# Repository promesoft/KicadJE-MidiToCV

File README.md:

# Kicad-MidiToCV
Midi to CV in Eurorack or as standalone

## Status - Rev B - Ongoing PCB layout and Sch update
Set on hold - MK2 is in progress ATM
## Status - Rev A Mounted - Midi code in progress
| Stage  | Detail | Status |
| ------------- | ------------- | ------------- |
| create material  | sch/pcb | produced Rev A  |
| | gerber | produced and uploaded RevA |
| production  | ordered  | OK |
|  | produced | OK |
|  | delivered | OK |
| ------------- | ------------- | ------------- |
| SOFTWARE | LFO | OK |
| SOFTWARE | MIDI MAP | OK - Stage 1 |
| SOFTWARE | CV | Ongoing |

## Preliminary validation
| Test  | Detail | Status |
| ------------- | ------------- | ------------- |
| Initial Inspection | Visual - Component Mounting | NOT OK |
| Initial Technical Test | Base operation | MIDI OUT NOT OK |
| | Knobs | OK |
| Initial Technical Test | MIDI IN | OK |
| Initial Technical Test | MIDI OUT | OK (to USB adapter) |
| Initial Product Test | MIDI IN/OUT MAPPER| OK |
| Initial Product Test | MIDI IN / CV OUT / GATE OUT| OK |
| Initial Product Test | LFO OUT| OK (use different pinout) |

## Secondary validation
| Test  | Detail | Status |
| ------------- | ------------- |------------- |
| Product Test | MIDI IN/OUT| OUT - FAIL on Roland keyboard |
| Product Test | LFO on DIO6 and 9 with ext RC | OK ! |
| Quality | LFO | Very usable |
| Quality | MIDI IN | |
| Quality | MIDI to CV | |
| Quality | MIDI to GATE | |
| Long Term Product Test | MIDI IN |  |
| Long Term Product Test | CV OUT |  |
| Long Term Product Test | GATE OUT |  |
| Long Term Product Test | LFO OUT | OK |
### Issues and Notes
Please note that the PIN1 and PIN2 are GATE. This is note described clearly in http://www.doepfer.de/a100_man/a100t_e.htm and needs to be noted when soldering the IDC header or when cabling if a Pin header has been mounted.
 * The two pots on the breakout board are too close for adding a knob
 * The orientation of the pinheader for the MCP4725 module - if mounted incorrectly the magic smoke disappears
 * 0R could be replaced with SMD jumpers
 * Consider a 200 mA fuse for Vin and 50mA for +5V pwr
 * The mounting hole that is off center is not matching both boards
### Errata
 * Footprint of PJ-321 has too small drill holes (1mm) - major
 * Footprint of PJ-321 is too narrow in the rear end :) - minor issue
 * Midi out circuit is WRONG - Major
### Workarounds
* Midi out not working - PCB workaround mod partially possible for voltage controlled inputs.
 * --Remove GND around DIN pin 5 (bottom copper side)
 * --Cut GND track to DIN pin 5 (top copper side)
 * --Remove Q1, R6, R9
 * --Connect 220R THT to base pad on Q1
 * --Connect C and E on Q1
 * --Add GND wire to pin2 of MIDI out DIN
## Physical Construction
 - 100x100mm
 - Separate unit with no alteration
 - Optional split in 2 for eurorack mount mirrored config

## Vital Components
 - Arduino Nano - where the magic lives (remember to socket it to be able to reprogram it)
 - Jack connectors: PJ-321 (important for the footprint)
 - KY-40 Encoder module (important for the pullup, footprint and 3D alignment)
 - MCP4825 module - if chosen (important for CV out function - footprint needs to match)
 If these are chosen the last two CV jacks should be ommitted.
 - MCP4728 chip - if chosen (important for the last 2 CV out)

## MIDI Board Features
### Single board - MIDI I/O and MIDI to CV
The board can be used as is for a prototype development of MIDI to CV
### Split board Eurorack - MIDI I/O and MIDI to CV
The board can be devided in two and combined front to front with spacers for a MIDI to CV eurorack module.
### Base board Eurorack - MIDI I/O
If only MIDI features are required the base board can work without the IO section.

## Generic Board Features
### Split board Options
The main board (with the arduino) has a couple of headers that can be connected to a different interface board using I2C, Analogue Inputs and Digital I/O.
### Non MIDI board
The MIDI components can be omitted if the features does not require MIDI, like an LFO, VCO or ADSR circuit.

## Base Construction
Arduino Nano based Controller and MIDI decoder.

### MIDI In
MIDI In through a PC814 (or optional PC817) Optocoupler and into the RX pin on the Arduino

### Midi Out
Optional expansion

### Gate
Gate pins from Arduino

## CV Out
I2C Dac with 2 options
### I2C Dac - Option 1 - Two Single channel DAC
2x MCP4725 DAC 
### I2C Dac - Option 2 - One 4 channel DAC
1x MCP4728

# RevB

# RevA

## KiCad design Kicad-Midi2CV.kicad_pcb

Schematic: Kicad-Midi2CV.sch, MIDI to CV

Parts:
A1: Arduino_Nano_v3.x; Arduino_Nano
C1: 100uF; CP_Radial_D5.0mm_P2.50mm
C2, C3, C5, C7, C8: 100n; C_0805_2012Metric_Pad1.15x1.40mm_HandSolder
C4, C6: 100uF 16v; CP_Radial_D5.0mm_P2.50mm
C9, C10, C11: 10n; C_0805_2012Metric_Pad1.15x1.40mm_HandSolder
D1: LED1; LED_D3.0mm_Horizontal_O6.35mm_Z6.0mm
D2: LED2; LED_D3.0mm_Horizontal_O6.35mm_Z6.0mm
D3: LED3; LED_D3.0mm_Horizontal_O6.35mm_Z6.0mm
D4: LED4; LED_D3.0mm_Horizontal_O6.35mm_Z6.0mm
D5: LEDset1; LED_D3.0mm_Horizontal_O6.35mm_Z6.0mm
D6: LEDset2; LED_D3.0mm_Horizontal_O6.35mm_Z6.0mm
IC1, IC2: MCP4725module; PinSocket_1x06_P2.54mm_Vertical
J1: Doepfer connector; PinSocket_2x08_P2.54mm_Vertical
J2: Vin 7-12v; BarrelJack_CUI_PJ-063AH_Horizontal
J3: MIDI OUT; din-5
J4: CV6 in; AudioJack3StereoNarrow-PJ-321
J5: Power Conn; PinHeader_1x04_P2.54mm_Vertical
J6: CV1; AudioJack3StereoNarrow-PJ-321
J7: CV2; AudioJack3StereoNarrow-PJ-321
J8: MIDI IN; din-5
J9: CV3; AudioJack3StereoNarrow-PJ-321
J10: CV4; AudioJack3StereoNarrow-PJ-321
J11: Gate1; AudioJack3StereoNarrow-PJ-321
J12, J18: GateConn; PinSocket_1x06_P2.54mm_Vertical
J13: Gate2; AudioJack3StereoNarrow-PJ-321
J14: Gate3; AudioJack3StereoNarrow-PJ-321
J15: Gate4; AudioJack3StereoNarrow-PJ-321
J16, J17: I2C_Conn; PinSocket_1x06_P2.54mm_Vertical
J19: CV7 in; AudioJack3StereoNarrow-PJ-321
J20: CV3 in; AudioJack3StereoNarrow-PJ-321
Q1, Q2: MMBT2222A; SOT-23_Handsoldering
R1, R2, R4, R5, R8, R10, R24, R25, R26, R27, R28: 10k; R_0805_2012Metric_Pad1.15x1.40mm_HandSolder
R3: 10M; R_0805_2012Metric_Pad1.15x1.40mm_HandSolder
R6, R9, R13, R15, R29: 1k; R_0805_2012Metric_Pad1.15x1.40mm_HandSolder
R7, R14: 220R; R_0805_2012Metric_Pad1.15x1.40mm_HandSolder
R11, R12: 8k2; R_0805_2012Metric_Pad1.15x1.40mm_HandSolder
R16, R17: 0R; R_0805_2012Metric_Pad1.15x1.40mm_HandSolder
R18, R19, R20, R21, R22, R23: 680R; R_0805_2012Metric_Pad1.15x1.40mm_HandSolder
RV1, RV2: 10k; Potentiometer_Alps_RK097_Single_Horizontal
SW1: KY40_Rotary_Encoder_Module; KY-40-rotary-encoder-board
U1: TL072; AJ_SO-8_5.3x6.2mm_P1.27mm
U2: EL814; DIP-4_W7.62mm_LongPads
U3: MCP4728; MSOP-10_3x3mm_P0.5mm

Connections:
+5V: A1.27, C3.2, IC1.5, IC2.5, J1.5, J1.6, J5.2, J16.6, J17.6, R3.1, R6.2, R11.2, R12.2, R13.2, SW1.5V, U2.4, U3.1
/12v: C4.1, C5.2, J1.7, J1.8, U1.8 (V+)
/-12v: C6.2, C7.1, J1.15, J1.16, U1.4 (V-)
/CV: J1.3, J1.4, R29.2
/Gate: J1.1, J1.2
/LDAC: A1.16, J16.4, J17.4, U3.4
/MIDI-IN: Q2.1, R15.2, U2.3
/MIDI-OUT: Q1.3, R6.1, R7.1
/RDY-BSY: A1.15, J16.5, J17.5, U3.5
/RX: A1.2, Q2.3, R13.1
/SCL: A1.24, IC1.3, IC2.3, J16.2, J17.2, R12.1, U3.2
/SDA: A1.23, IC1.4, IC2.4, J16.3, J17.3, R11.1, U3.3
/TX: A1.1, Q1.1, R9.2
/Vout1: IC1.1, R16.2
/Vout2: IC2.1, R17.2
A1: A1.20, C10.1, SW1.CLK
A2: A1.21, C11.1, SW1.DT
A3: A1.22, R27.2, R28.1
A6: A1.25, J12.5, J18.5, R8.2, R10.1
A7: A1.26, J12.6, J18.6, R25.2, R26.1, R29.1
Btn: A1.19, C9.1, R24.1
CV1: R16.1, U1.3 (+), U3.6
CV1Gain: J6.T, RV1.2, RV1.3, U1.1
CV2: R17.1, U1.5 (+), U3.7
CV2Gain: J7.T, RV2.2, RV2.3, U1.7
CV3: J9.T, U3.8
CV4: J10.T, U3.9
GND: A1.4, A1.29, C1.2, C2.2, C3.1, C4.2, C5.1, C6.1, C7.2, C8.1, C9.2, C10.2, C11.2, D1.1, D2.1, D3.1, D4.1, D5.1, D6.1, IC1.2, IC1.6, IC2.2, IC2.6, J1.9, J1.10, J1.11, J1.12, J1.13, J1.14, J2.2, J3.5, J4.S, J5.4, J6.S, J7.S, J9.S, J10.S, J11.S, J13.S, J14.S, J15.S, J16.1, J17.1, J19.S, J20.S, Q1.2, Q2.2, R4.2, R5.2, R9.1, R10.2, R15.1, R26.2, R28.2, SW1.GND, U3.10
Gate1: A1.9, J11.T, J12.1, J18.1
Gate2: A1.10, J12.2, J13.T, J18.2
Gate3: A1.11, J12.3, J14.T, J18.3
Gate4: A1.12, J12.4, J15.T, J18.4
LED1: A1.5, R18.1
LED2: A1.6, R19.1
LED3: A1.7, R20.1
LED4: A1.8, R21.1
LED-sel: A1.13, R22.1
LED-sel2: A1.14, R23.1
unnamed: A1.17, C8.2, J5.3
unnamed: D1.2, R18.2
unnamed: D2.2, R19.2
unnamed: D3.2, R20.2
unnamed: D4.2, R21.2
unnamed: D5.2, R22.2
unnamed: D6.2, R23.2
unnamed: J3.4, R7.2
unnamed: J4.T, R8.1
unnamed: J8.4, R14.2
unnamed: J8.5, U2.2
unnamed: J19.T, R25.1
unnamed: J20.T, R27.1
unnamed: R1.1, RV1.1
unnamed: R1.2, R4.1, U1.2 (-)
unnamed: R2.1, RV2.1
unnamed: R2.2, R5.1, U1.6 (-)
unnamed: R14.1, U2.1
unnamed: R24.2, SW1.SW
VCC: A1.30, C1.1, C2.1, J2.1, J5.1, R3.2

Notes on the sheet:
MIDI IN
LED Signals
Encoder Control
I2C DAC
POWER
MIDI OUT
Board intercon

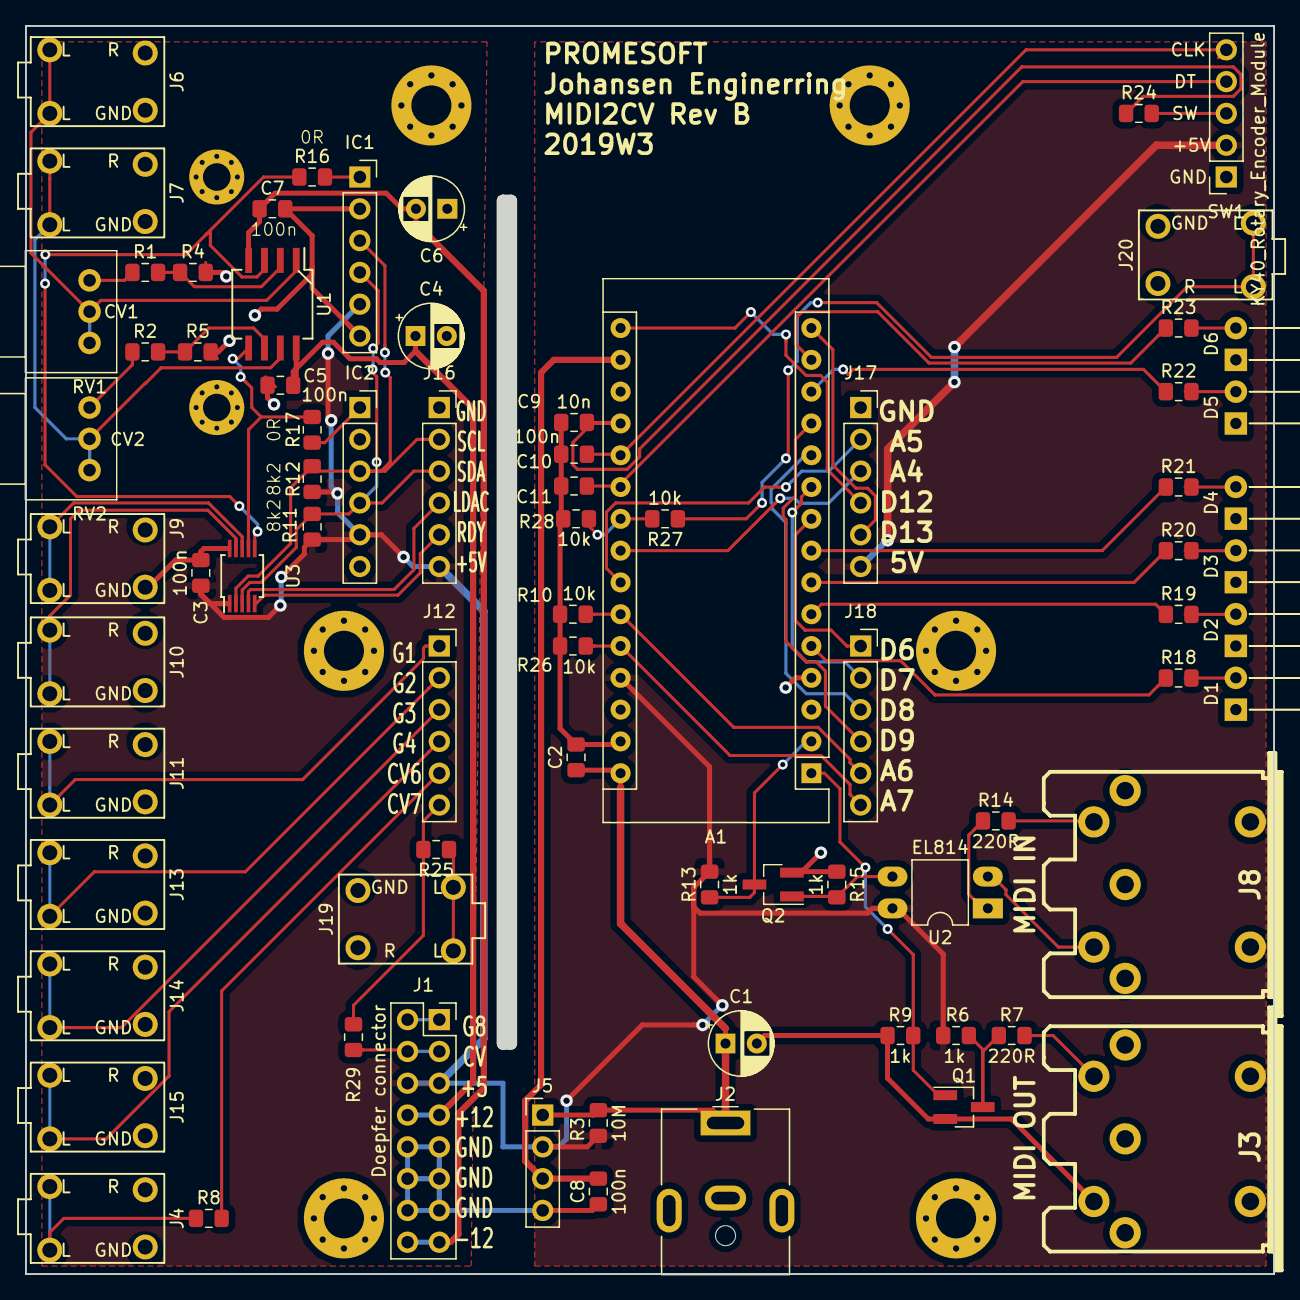
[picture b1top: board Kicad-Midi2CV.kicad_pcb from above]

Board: 2 copper layers, 98.8 x 98.8 mm, 77 parts (0 on the bottom side), 58 nets.

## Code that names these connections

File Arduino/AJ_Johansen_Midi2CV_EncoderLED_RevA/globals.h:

/* -----------------------------------------------
 *  GLOBAL DEFINES
 * -----------------------------------------------
 */
#define SWpin A0 //add 10nF to GND for debounce (not essential
#define Apin A1 //add 47nF/100nF to GND for debounce
#define Bpin A2 //add 47nF/100nF to GND for debounce
#define CV3in A3
#define SDA A4
#define SCL A5
#define CV6in A6
#define CV7in A7

#define LED1 2
#define LED2 3
#define LED3 4
#define LED4 5
#define LEDsel 10
#define LEDsel2 11

#define Gate1 6
#define Gate2 7
#define Gate3 8
#define Gate4 9

#define RDY-BSY 12
#define LDAC 13

/* -----------------------------------------------
 *  GLOBAL VAR
 * -----------------------------------------------
 */
boolean A_old=0, B_old=1, SW_old=0;
boolean left = false, right = false, button = false;

//Structure for keeping MIDI CH data for LED
boolean LEDData[4][4]; //(see state)

boolean LEDSelData = false, LEDSel2Data = false; 
unsigned int encoder[4], buttoncnt = 0;
unsigned int state = 0; //State 00 = MidiDataInChannel - 01 = MIDI CH in select - 10 = MIDI CH OUT select - 11 = MIDI CH 2 CV select

//byte midi_channel=4;
//Structure for keeping MIDI CH data for processing
byte MIDI_CH[4]; //(see state)


/* -----------------------------------------------
 *  PROTOTYPES
 * -----------------------------------------------
 */
void MyHandleNoteOn(byte channel, byte pitch, byte velocity);
void MyHandleNoteOff(byte channel, byte pitch, byte velocity);

/*void checkencoder();
//void updateLEDValue(unsigned int nibble,unsigned int updstate);
void updateLED();
void clearLED();
*/

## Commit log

2018-12-20 Project Initiated
    Core components added
    Initial wiring performed
    Grid 50mil
2018-12-20 GND and LED
    GND added
    MIDI CH LED indicators added
2018-12-20 I2C
    Power and pullup
2018-12-20 reorganize
    boxes around functions
2018-12-20 MIDI pinout
    correct
2018-12-20 DIN-5 footprint
    added from http://smisioto.no-ip.org/elettronica/kicad/kicad-en.htm
2018-12-20 Channel select
    Rotary encoder added for MIDI channel select
2018-12-20 Footprints
    Cap, BJT, Conn, Etc
2018-12-21 Footprints
    footprint PL814
2018-12-22 mini in
    adj
2018-12-25 Power +5V
    Misc power and resistors near encoder
2018-12-25 misc
    misc
2018-12-26 Power redraw
    Redraw power
2018-12-26 Jack
    PJ398SM x2 jack
2018-12-26 LED tag
    Labels for LED, button, encoder and Gates
2018-12-26 Multi IO
    Gate3/4
    Encoder to A0, A1, A2
    A3 as input
    LED sel2
2018-12-26 Netlist
    update temp
2018-12-26 Rev A ------- before check
    9 Jacks attached
    Slight rearrange
2018-12-26 Rev A2 - prior to footprint
    CV1 and CV2 with gain adjustment
2018-12-26 MIDI Out
    Misc Cleanup
2018-12-26 Footprints
    Rotary encoder should be replaced...
2018-12-27 PCB RevA - need new footprints and update 3D
    Board split in 2
2018-12-28 Replace PJ301 w PJ321
2018-12-28 Jack I/O
    Label jacks
    Voltage div on CV in / A3
2018-12-28 Names to remaining IO
    MIDI
    LED
    Pots are kept as RV1 and RV2 as it matches CV1 and CV2
    Front panel rearranged
2018-12-28 PCB misc
2018-12-28 PCB
    Misc - minor
2018-12-29 Fixed Analog voltage
    Encoder module replace
    PCB reorganize
    Added Analogue supply - not done
    changed Jacks
    etc
2018-12-29 Board interconnectors
    Gate and I2C signals prepared
2018-12-29 organizing PCB placement
2018-12-29 Interconn footprint adj
2018-12-29 Update _saved_Kicad-Midi2CV.sch
    Swap SCL and SDA in board interconnector
2018-12-29 Reorganize PCB
    make sure the board assembles when sandwiched
2018-12-29 Analogue card routed - no GND
2018-12-30 fix OP Amp mistake
    SCH, ERC and Netlist
2018-12-30 AJ-SO8
2018-12-30 AJ_SO8 pad for Op Amp
2018-12-30 Initial routing on CPU side
2018-12-30 Before planes...
2018-12-30 RevA PCB
2018-12-30 PCB Final Trim
    Silk adj:
    Text adjustments
    Label board x2
    Label headers
    Add values to resistors on silk
    Power lanes beefed up (0,5 or 0,6) when long or feed.
2018-12-30 Gerber
    Gerber and Drill for JLC
2019-01-02 Gerber and Printouts
2019-01-09 physical
2019-01-09 Update README.md
    Split and single board
2019-01-09 Update README.md
    MIDI2CV_sch.pdf
2019-01-09 Update README.md
    MIDI2CV_sch.png
2019-01-09 MIDI2CV_sch.png
2019-01-09 Update README.md
    alternatives
2019-01-15 3D Visualisations
2019-01-21 RevA Archived - RevB Initiated
    PJ-321 footprint drill increased from 1mm to 1,2mm and rear holes narrower
2019-01-21 R and C Labels on analogue side
2019-01-21 Rev B PCB - SCH - Images
2019-01-21 Minor
2019-01-24 Initial Arduino Sketch
2019-01-24 Iteration2 - XPS (no compile? no test!)
    Update filename - restructure LED out - select LED counter
2019-01-26 Arduino - Sel and Sel2 works
    only compiles on windows store edition - 1.8.8 complains abt ISR (PCINT1_vect) {
2019-01-27 Arduino code - separate states for all 4 led sections
2019-01-27 Arduino - Midi input - show channel on LED state 0
2019-01-27 Pictures
2019-01-29 Arduino - Mapping Incomming MIDI channel to state1 channel
2019-01-29 Arduino - Initial working prototype
    :oD
2019-01-29 Update AJ_Johansen_Midi2CV_EncoderLED_RevA.ino
    Header update
2019-01-29 Workaround mod for MIDI out
2019-01-29 Workaround section
2019-01-30 Updated Midi out
    initial failsafe with lots of extra optional components
2019-01-30 Overengineered MIDI out
    To accomodate for almost all eventialities the MIDI out now consists of 10 resistors and one transistor....A NO jumper has been installed for the GND to shield of the DIN conn.
2019-01-30 MIDI out JP3 footprint changed to closed JP
2019-01-30 Persisting MIDI selection in EEPROM
2019-01-31 New Front plate design for RevB (MK2.1)
2019-02-10 Arduino LFO
2019-02-11 Arduino - dual LFO sine+triangle
2019-02-11 Aruino - LFO merging with MIDI
2019-02-11 Arduino - LFO state added
2019-02-11 Arduino - first working prototype
2019-02-15 Arduino - Mem optimized for LFO Quad out
    Quad out: 2 PWM shapes out, square and inv square out
2019-02-15 Arduino - Quad LFO Working nicely :)
    Tested with VCF and DRone
2019-02-15 Update AJ_LFO_quad_out.ino
    LFO 15 changed from dirac to 2xfreq
2019-03-11 Arduino - CV control ch1 - Gate control ch1
2019-03-12 Arduino - 2xCV and Gate
